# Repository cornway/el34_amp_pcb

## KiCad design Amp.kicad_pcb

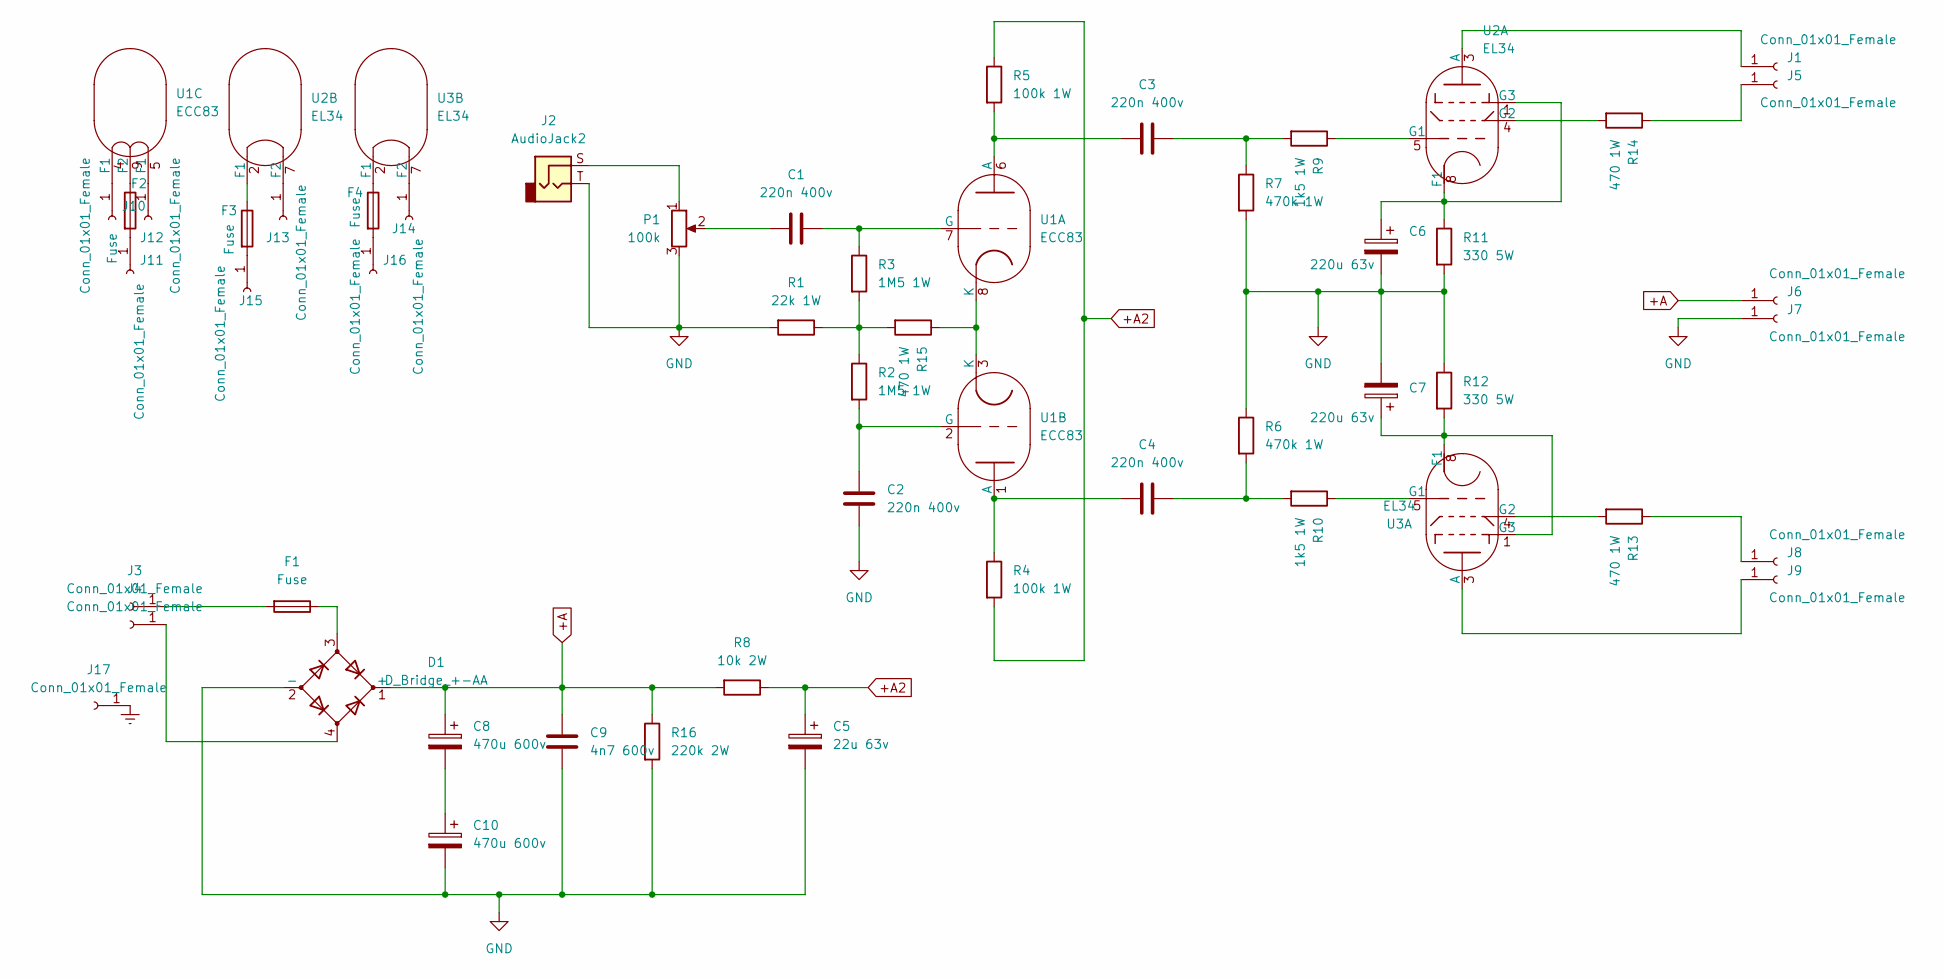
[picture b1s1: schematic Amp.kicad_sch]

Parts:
C1, C2, C3, C4: 220n 400v; C_Rect_L16.5mm_W5.0mm_P15.00mm_MKT
C5: 22u 63v; CP_Radial_D6.3mm_P2.50mm
C6, C7: 220u 63v; C_Radial_D10.0mm_H16.0mm_P5.00mm
C8, C10: 470u 600v; CP_Radial_D40.0mm_P10.00mm_SnapIn
C9: 4n7 600v; C_Rect_L16.5mm_W5.0mm_P15.00mm_MKT
D1: D_Bridge_+-AA; Diode_Bridge_32.0x5.6x17.0mm_P10.0mm_P7.5mm
F1, F2, F3, F4: Fuse; Fuseholder_Cylinder-5x20mm_Schurter_0031_8201_Horizontal_Op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
J1, J3, J4, J5, J6, J7, J8, J9, J10, J11, J12, J13, J14, J15, J16, J17: Conn_01x01_Female; Pin_D1.0mm_L10.0mm
J2: AudioJack2; Jack_3.5mm_CUI_SJ-3523-SMT_Horizontal
P1: 100k; Potentiometer_TT_P0915N
R1: 22k 1W; R_Axial_DIN0414_L11.9mm_D4.5mm_P20.32mm_Horizontal
R2, R3: 1M5 1W; R_Axial_DIN0414_L11.9mm_D4.5mm_P20.32mm_Horizontal
R4, R5: 100k 1W; R_Axial_DIN0414_L11.9mm_D4.5mm_P20.32mm_Horizontal
R6, R7: 470k 1W; R_Axial_DIN0414_L11.9mm_D4.5mm_P20.32mm_Horizontal
R8: 10k 2W; R_Axial_DIN0516_L15.5mm_D5.0mm_P20.32mm_Horizontal
R9, R10: 1k5 1W; R_Axial_DIN0414_L11.9mm_D4.5mm_P20.32mm_Horizontal
R11, R12: 330 5W; R_Axial_Power_L25.0mm_W6.4mm_P30.48mm
R13, R14, R15: 470 1W; R_Axial_DIN0414_L11.9mm_D4.5mm_P20.32mm_Horizontal
R16: 220k 2W; R_Axial_DIN0516_L15.5mm_D5.0mm_P20.32mm_Horizontal
U1: ECC83; Valve_Noval_P
U2, U3: EL34; Valve_Octal

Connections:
+A: C8.1, C9.2, D1.1 (+), J6.1, R8.2, R16.1
+A2: C5.1, R4.2, R5.1, R8.1
Earth: J17.1
GND: C2.1, C5.2, C6.2, C7.2, C9.1, C10.2, D1.2 (-), J2.T, J7.1, P1.3, R1.2, R6.1, R7.2, R11.2, R12.1, R16.2
unnamed: C1.1, R3.1, U1.7 (G)
unnamed: C1.2, P1.2
unnamed: C2.2, R2.2, U1.2 (G)
unnamed: C3.1, R7.1, R9.2
unnamed: C3.2, R5.2, U1.6 (A)
unnamed: C4.1, R6.2, R10.2
unnamed: C4.2, R4.1, U1.1 (A)
unnamed: C6.1, R11.1, U2.1 (G3), U2.8 (F1)
unnamed: C7.1, R12.2, U3.1 (G3), U3.8 (F1)
unnamed: C8.2, C10.1
unnamed: D1.3, F1.1
unnamed: D1.4, J4.1
unnamed: F1.2, J3.1
unnamed: F2.2, J11.1
unnamed: F3.2, J15.1
unnamed: F4.2, J16.1
unnamed: J2.S, P1.1
unnamed: R1.1, R2.1, R3.2, R15.2
unnamed: R9.1, U2.5 (G1)
unnamed: R10.1, U3.5 (G1)
unnamed: J8.1, R13.1
unnamed: R13.2, U3.4 (G2)
unnamed: J5.1, R14.1
unnamed: R14.2, U2.4 (G2)
unnamed: R15.1, U1.3 (K), U1.8 (K)
unnamed: J10.1, U1.4 (F1)
unnamed: J12.1, U1.5 (F1)
unnamed: F2.1, U1.9 (F2)
unnamed: F3.1, U2.2 (F1)
unnamed: J1.1, U2.3 (A)
unnamed: J13.1, U2.7 (F2)
unnamed: F4.1, U3.2 (F1)
unnamed: J9.1, U3.3 (A)
unnamed: J14.1, U3.7 (F2)

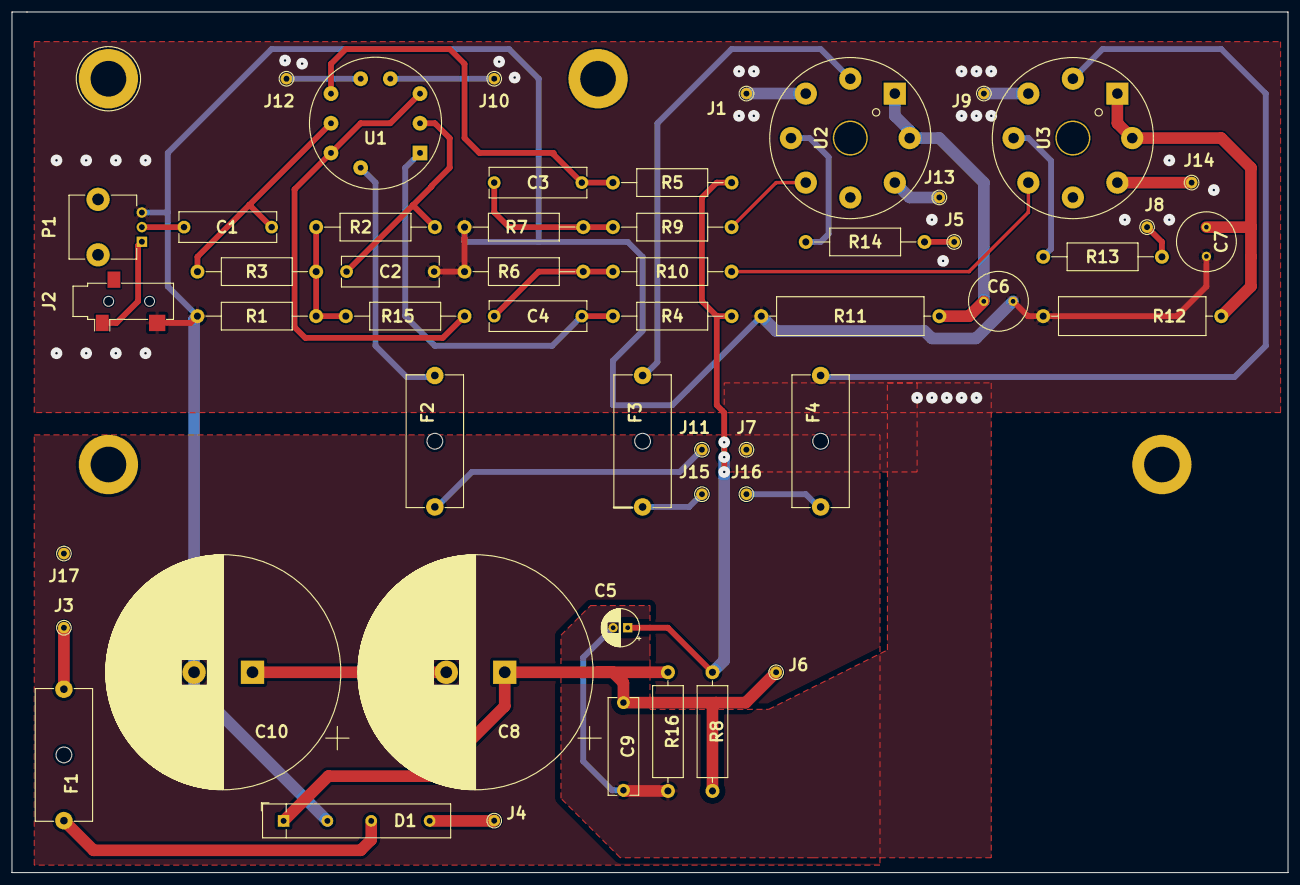
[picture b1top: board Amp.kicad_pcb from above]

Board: 2 copper layers, 218.4 x 147.3 mm, 53 parts (0 on the bottom side), 37 nets.

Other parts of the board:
REF: Banana_Jack_1Pin

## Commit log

2021-12-30 Initial chematic
2022-01-03 Some updates
2022-01-03 Adding footprints
2022-01-08 Update, cleanup
2022-01-10 Cosmetic/cleanup
